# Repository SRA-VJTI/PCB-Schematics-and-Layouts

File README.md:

# PCB Schematics and Layouts
This Repository contains the schematic and layout files for all the PCBs designed at SRA for various competitions and workshops.

- **Robocon PCBs 2016**  
  PCB files made for the *Manually Operated Robot* in **Robocon 2016**.  
  Designed on **Autodesk EAGLE CAD**.  
  - **128 breakout**  
    - This is the breakout board for the *Atmega 128 Microcontroller* SMD Package.  
    - It also consists the External Clock Circuit and a connector slot for the programmer cable.  
  - **Main Board**  
    - The microcontroller breakout circuit is mounted on this pcb.  
    - It contains peripherals like input switches & LEDs, fuses for short-circuit protection and various connectors to connect sensors & actuators to the controller.  
    
- **Robocon PCBs 2017**  
  PCB files made for the *Manually Operated Robot* in **Robocon 2017**.  
  Designed on **Autodesk EAGLE CAD**.  
  - **128 breakout**  
    - This is the breakout board for the *Atmega 128 Microcontroller* SMD Package.  
    - It also consists the External Clock Circuit and a connector slot for the programmer cable.  
  - **Main Board**  
    - The microcontroller breakout circuit is mounted on this pcb.  
    - It contains peripherals like input switches & LEDs, fuses for short-circuit protection and various connectors to connect sensors & actuators to the controller.  
  - **Line Sensing Array**  
    - It contains a sensor array to detect different colors to help follow a line.  
  - **Power and Motor Control Breakout**  
    - It contains the circuit to connect several motor drivers to a single connector.  
    - It also has a Relay-based braking ciruit to pyhsically short the DC motor terminals.  
    - This PCB also contains the voltage regulators to power the microntroller circuits as well as the motor controllers.  

- **WallE 2016 Dev Brd**  
  - PCB files made for the **Line-follower Robot Workshop (WallE)** in the year 2016.  
  - It uses an **Atmega 16 Microcontroller** in its DIP package, with peripherals like input switches & LEDs, fuses for short-circuit protection, external clock circuit, programmer slot and various connectors to connect sensors & actuators to the controller.  
  - Designed on **KiCAD**.  

- **WallE 2.0 2017 Dev Brd**  
  - PCB files made for the **Line-follower and Self-Balancing Robot Workshop (WallE 2.0)** in the year 2017.  
  - Compared to the 2016 Dev Brd, this iteration has an extra slot to connect an MPU6050 inertial sensor.  
  - Designed on **Autodesk EAGLE CAD**.  

- **MPU Board**  
  - PCB files made for the **MPU 6050** inertial sensor breakout board, used in the **Self-balancing Robot Workshop (WallE 2.0)**.   
  - It has onboard *Pull-up resistors* for the *I2C protocol* lines (SCL and SDA).  
  - Connects to the main Dev Board through a 6 pin Flat Ribbon Cable.  
  - Designed on **Autodesk EAGLE CAD**.  

- **WallE 2.1 2018 Dev Brd**  
  - PCB files made for the **Line-follower and Self-Balancing Robot Workshop (WallE 2.1)** in the year 2018.  
  - It uses an **Espressif System's ESP32** SoC DevKit, with peripherals like input switches & LEDs, fuses for short-circuit protection, external clock circuit and various connectors to connect sensors & actuators to the controller.  
  - Designed on **Autodesk EAGLE CAD**.  

- **ESP 8266 Board**  
  - PCB files made for the **IOT Workshop** in the year 2016.  
  - It uses **Espressif System's ESP 8266** SoC.  
  - Contains a switch to toggle between flash mode and GPIO mode. 
  - Designed on **Autodesk EAGLE CAD**.

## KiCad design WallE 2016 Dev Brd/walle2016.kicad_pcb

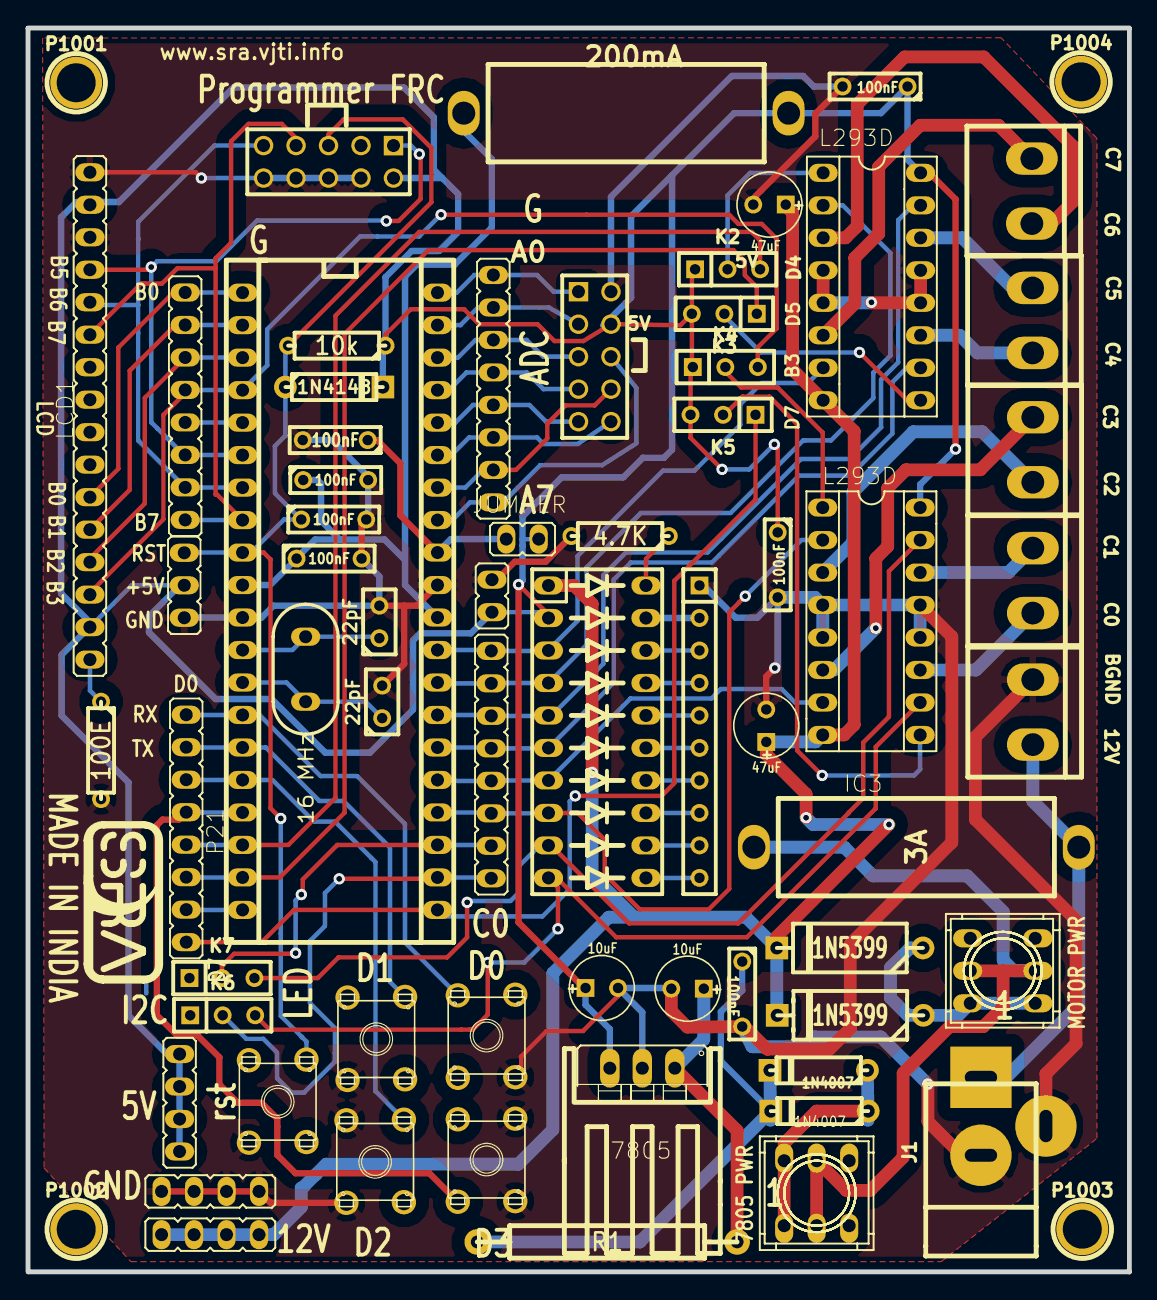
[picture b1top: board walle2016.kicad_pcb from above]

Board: 2 copper layers, 86.1 x 97.3 mm, 68 parts (0 on the bottom side), 57 nets.

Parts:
BAR1: DOT-BAR2; DOT-BAR
C1, C2, C3, C4, C5, C6, C7: 100nF; C2
C8, C9: 10uF; C1V5
C10, C11: 22pF; C1
C12, C13: 47uF; C1V5
D1, D2: 1N4007; D3_c
D3: 1N4148; D3_c
D4, D5: 1N5399; D4-5_c
F1: 200mA; Fuse
F2: 3A; Fuse
IC1: ATMEGA16-P; DIP-40_600_ELL_c
IC2, IC3: L293D; DIL16_c
J1: JACK_2P; JACK_ALIM
JP1: JUMPER; pin_array_c_2
K1: CONN_3; pin_array_c_3
K2, K3, K4, K5, K6, K7: CONN_3; MICROSWITCH_SPST
LCD1: LCD_2X16_SIL; pin_array_c_16
P1, P3, P4, P5, P6: CONN_2; Wire_Conn
P7, P8, P22: CONN_4; pin_array_c_4
P9, P13: CONN_5X2; PIN_ARRAY_5x2
P17: CONN_2; pin_array_c_2
P19, P20, P21, P101: CONN_8; pin_array_c_8
P1001, P1002, P1003, P1004: CONN_1; 1pin
R1: 2W_RES; 2wres
R2: 10k; R3
R5: 4.7K; R3
R6: 100E; R3
RR1: RR9; r_pack9
S1, S2, S3, S4, S5: FSMCD; switch-misc-FSMCD
SRA_logo: VAL**; SRA_logo_silk_new
SW1001, SW1002: DUAL_SWITCH_INV; DPDT_switch_c
U1: 7805; TO220V_HS
X1: 16 MHz; Crystal

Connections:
+5V: BAR1.2, C6.1, C7.1, C9.1, D3.2, F1.1, IC2.16, IC3.16, JP1.1, K1.2, K2.1, K3.3, K4.1, K5.3, LCD1.2, LCD1.15, P7.1, P7.2, P7.3, P7.4, P9.4, P13.2, P17.2, R2.1, U1.3
/A0: IC1.40, P9.1, P101.8
/A1: IC1.39, P9.3, P101.7
/A2: IC1.38, P9.5, P101.6
/A3: IC1.37, P9.7, P101.5
/A4: IC1.36, P9.9, P101.4
/A5: IC1.35, P9.10, P101.3
/A6: IC1.34, P9.8, P101.2
/A7: IC1.33, P9.6, P101.1
/B0: IC1.1, LCD1.11, P19.8
/B1: IC1.2, LCD1.12, P19.7
/B2: IC1.3, LCD1.13, P19.6
/B3: IC1.4, K4.3, LCD1.14, P19.5
/B4: IC1.5, P19.4
/B5: IC1.6, LCD1.4, P13.1, P19.3
/B6: IC1.7, LCD1.5, P13.9, P19.2
/B7: IC1.8, LCD1.6, P13.7, P19.1
/C0: BAR1.10, IC1.22, IC3.10, K6.2, K6.3, P20.8
/C1: BAR1.9, IC1.23, IC3.15, K7.2, K7.3, P20.7
/C2: BAR1.8, IC1.24, IC3.2, P20.6
/C3: BAR1.7, IC1.25, IC3.7, P20.5
/C4: BAR1.6, IC1.26, IC2.10, P20.4
/C5: BAR1.5, IC1.27, IC2.15, P20.3
/C6: BAR1.4, IC1.28, IC2.2, P20.2
/C7: BAR1.3, IC1.29, IC2.7, P20.1
/D0: IC1.14, P21.8, S2.P$4
/D1: IC1.15, P21.7, S3.P$3
/D2: IC1.16, P21.6, S4.P$3
/D3: IC1.17, P21.5, S5.P$3
/D4: IC1.18, K2.3, P21.4
/D5: IC1.19, K3.1, P21.3
/D6: IC1.20, P21.2
/D7: IC1.21, K5.1, P21.1
/vcc: F2.2, J1.1, P1.1
/~RST: C1.1, D3.1, IC1.9, K1.3, P13.5, R2.2, S1.P$3
GND: C1.2, C2.2, C3.2, C4.2, C6.2, C7.2, C10.2, C11.2, C12.2, C13.2, IC1.11, IC1.31, IC2.4, IC2.5, IC2.12, IC2.13, IC3.4, IC3.5, IC3.12, IC3.13, J1.2, J1.3, K1.1, LCD1.1, LCD1.3, P1.2, P8.1, P8.2, P8.3, P8.4, P9.2, P13.4, P13.6, P13.8, P13.10, P17.1, R5.2, R6.2, RR1.1, S1.P$2, S2.P$1, S3.P$2, S4.P$1, S4.P$2, S5.P$1, S5.P$2
unnamed: C2.1, C3.1, F1.2, IC1.10, IC1.30
unnamed: C10.1, IC1.12, X1.1
unnamed: C11.1, IC1.13, X1.2
unnamed: C8.1, R1.1, U1.1
unnamed: C5.2, C8.2, C9.2, U1.2
unnamed: C5.1, D1.2, D2.2, R1.2
unnamed: BAR1.20, R5.1
unnamed: BAR1.12, RR1.9
unnamed: BAR1.15, IC3.9, RR1.6
unnamed: BAR1.16, RR1.5
unnamed: BAR1.19, RR1.2
unnamed: BAR1.18, RR1.3
unnamed: D1.1, D2.1, SW1001.1, SW1001.6
unnamed: BAR1.14, RR1.7
unnamed: F2.1, SW1001.2, SW1001.5, SW1002.2, SW1002.5
unnamed: D4.1, D5.1, SW1002.1, SW1002.6
unnamed: C4.1, IC1.32, JP1.2
unnamed: BAR1.13, RR1.8
unnamed: BAR1.17, RR1.4
unnamed: BAR1.11, RR1.10
VAA: BAR1.1, C12.1, C13.1, D4.2, D5.2, IC2.8, IC3.8, P22.1, P22.2, P22.3, P22.4

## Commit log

2020-02-05 Add Gitignore File
2020-02-05 Add PCB files for Robocon 2016
2020-02-05 Add PCB files for WallE Workshop - 2016
2020-02-05 Add PCB files for MPU breakout board for WallE 2.0 Workshop
2020-02-05 Add PCB files for ESP8266 breakout for IOT Workshop 2016
2020-02-05 Add MIT License
2020-02-16 Add PCB files for WallE 2.0 Workshop
2020-02-16 Add PCB files for WallE 2.1 Workshop on ESP32
2020-02-16 Add PCB files for Robocon 2017
